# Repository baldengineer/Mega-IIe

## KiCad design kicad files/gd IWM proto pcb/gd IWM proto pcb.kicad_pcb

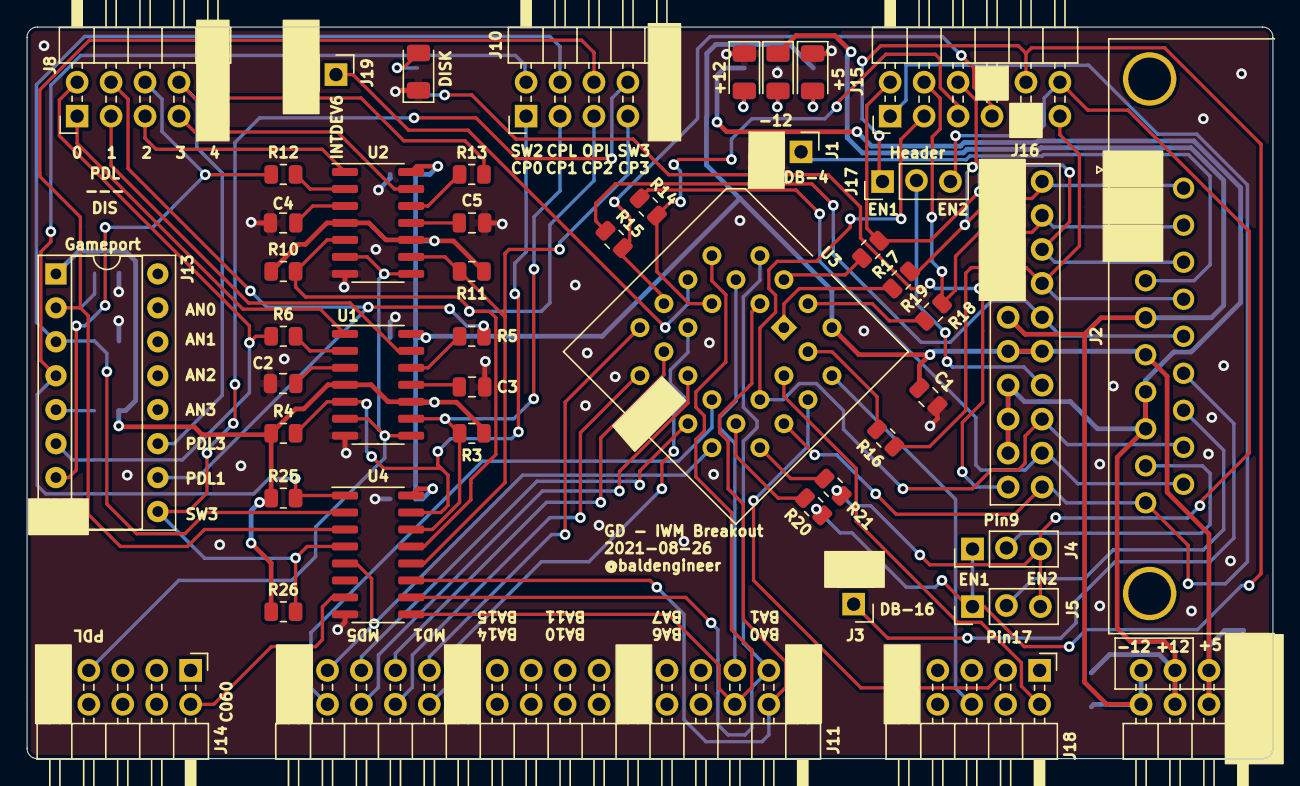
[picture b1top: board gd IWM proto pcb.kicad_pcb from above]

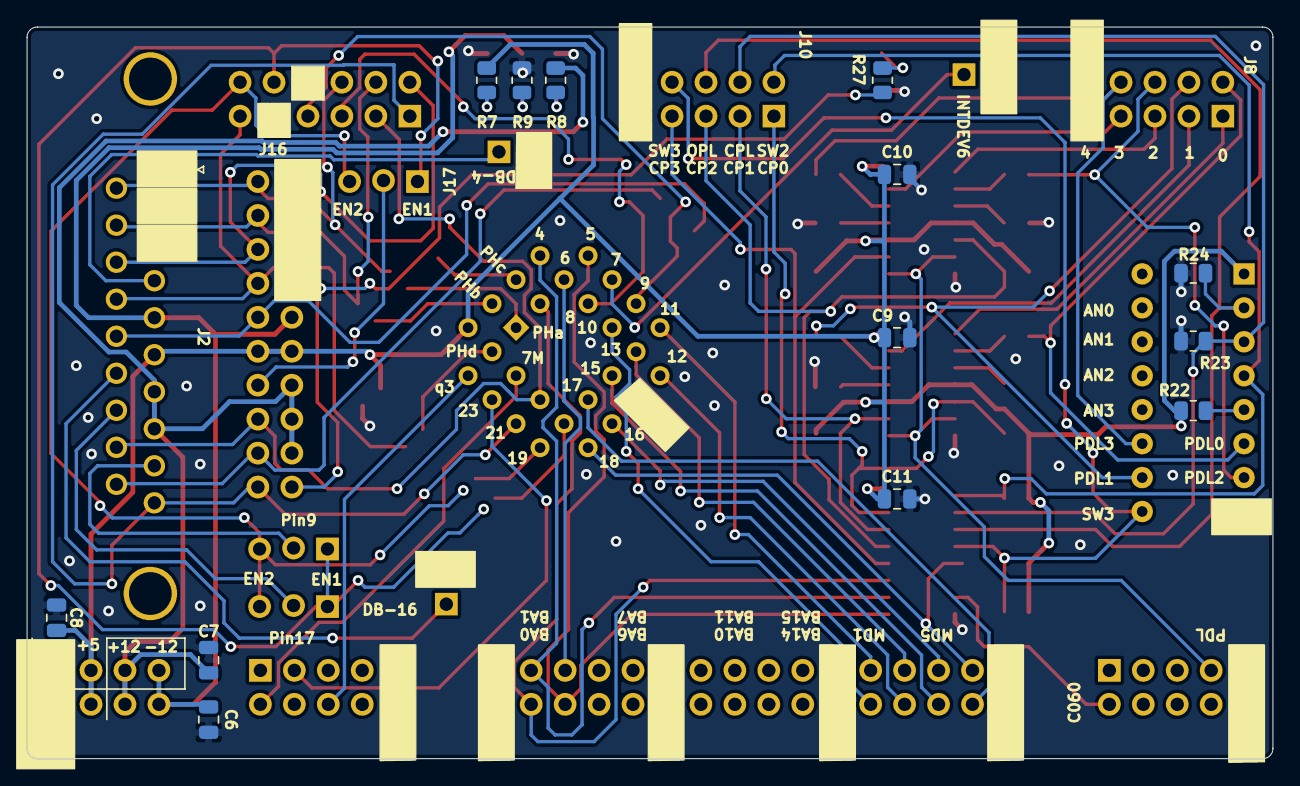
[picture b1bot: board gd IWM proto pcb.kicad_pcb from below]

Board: 2 copper layers, 93.2 x 54.7 mm, 60 parts (13 on the bottom side), 75 nets.

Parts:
C1, C6, C7, C8: 10u; C_0805_2012Metric
C2, C3, C4, C5: .1u; C_0805_2012Metric
C9, C10, C11: 1u; C_0805_2012Metric
D2: -5v; LED_1206_3216Metric
D3: +5v; LED_1206_3216Metric
D4: +12v; LED_1206_3216Metric
D5: DSK; LED_1206_3216Metric
J1: DB19_4; PinHeader_1x02_P2.54mm_Vertical-LOCK
J2: DSUB19; DSUB-19_Apple_II_Floppy
J3: DB19_16; PinHeader_1x02_P2.54mm_Vertical-LOCK
J4, J5, J17: EN; PinHeader_1x03_P2.54mm_Vertical-LOCK
J6: PWR; PinHeader_2x04_P2.54mm_Horizontal
J8: 555_LA; PinHeader_2x05_P2.54mm_Horizontal
J10: CPx_LA; PinHeader_2x05_P2.54mm_Horizontal
J11: Addr_Main_Data; PinHeader_2x16_P2.54mm_Horizontal
J13: Game Port; DIP-16_W7.62mm_Socket
J14: CTRL2; PinHeader_2x05_P2.54mm_Horizontal
J15: IWM-LA; PinHeader_2x06_P2.54mm_Horizontal
J16: FDC Hdr; PinHeader_2x10_P2.54mm_Vertical
J18: CTRL1; PinHeader_2x05_P2.54mm_Horizontal
J19: Slot_Maker; PinHeader_1x02_P2.54mm_Vertical-LOCK
R3, R4, R10, R11: 1K; R_0805_2012Metric
R5, R6, R12, R13: 100; R_0805_2012Metric
R7, R8, R9: 1k; R_0805_2012Metric
R14, R15, R16, R17, R18, R19, R20, R21: 22; R_0805_2012Metric
R22, R23, R24, R27: 4k7; R_0805_2012Metric
R25, R26: 200k; R_0805_2012Metric
U1, U2: NE556; SO-14_3.9x8.65mm_P1.27mm
U3: IWM; PLCC-28_THT-Socket
U4: HCT251; SOIC-16_3.9x9.9mm_P1.27mm

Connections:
+5V: C1.1, C8.1, C9.1, C10.1, C11.1, J2.6, J6.3, J6.4, J13.1, J16.11, J16.12, R3.1, R4.1, R7.1, R10.1, R11.1, R22.1, R25.1, R26.1, U1.4, U1.10, U1.14, U2.4, U2.10, U2.14, U3.26, U4.16
+12V: C7.1, J2.7, J2.8, J6.5, J6.6, J16.13, J16.15, J16.17, R8.1
-12V: C6.1, D2.1, J2.5, J6.7, J6.8, J16.9
/7M: J18.2, U3.24
/BA0: J11.4, U3.3, U4.11
/BA1: J11.3, U3.4, U4.10
/BA2: J11.6, U3.5, U4.9
/BA3: J11.5, U3.6
/C060-67: J14.2, U4.7
/CP0: J10.1, R4.2, U1.5, U4.15
/CP1: J10.3, R3.2, U1.9, U4.14
/CP2: J10.5, R10.2, U2.5, U4.13
/CP3: J10.7, R11.2, U2.9, U4.12
/DB19-4: J1.1, J2.4
/DB19-16: J2.16, J3.1
/DIS0: J8.1, U1.1
/DIS1: J8.3, U1.13
/DIS2: J8.5, U2.1
/DIS3: J8.7, U2.13
/DiskAct: J16.19, R27.1
/EN1: R20.2, U3.20
/EN2: R21.2, U3.19
/INTDEV6: J19.1, U3.7
/MD0: J11.24, U3.10
/MD1: J11.23, U3.11
/MD2: J11.26, U3.12
/MD3: J11.25, U3.13
/MD4: J11.28, U3.15
/MD5: J11.27, U3.16
/MD6: J11.30, U3.17
/MD7: J11.29, U3.18, U4.5
/PDL0: J8.2, J13.6, R6.1
/PDL1: J8.4, J13.10, R5.1
/PDL2: J8.6, J13.7, R12.1
/PDL3: J8.8, J13.11, R13.1
/PDLTRIG: J14.7, U1.6, U1.8, U2.6, U2.8
/PHa: R19.2, U3.1
/PHb: R18.2, U3.28
/PHc: R17.2, U3.2
/PHd: R16.2, U3.27
/Q3: J18.6, U3.25
/RDATA: J2.18, J15.3, J16.16, U3.22
/RESET: J18.3, U3.23
/SENSE: J2.10, J15.1, J16.20, U3.21
/STB: J13.5, R22.2
/SW0_OAPL: J10.6, J13.2, R24.1, U4.3
/SW1_CAPL: J10.4, J13.3, R23.1, U4.2
/SW2: J10.2, J13.4, R25.2, U4.1
/SW3: J10.8, J13.9, R26.2, U4.4
/WDATA: J15.5, R14.2, U3.8
/WREQ: J15.7, R15.2, U3.9
/bEN1: J4.1, J5.1, J15.10, J17.1, R20.1
/bEN2: J4.3, J5.3, J15.12, J17.3, R21.1
/bWDATA: J2.19, J16.18, R14.1
/bWREQ: J2.15, J16.10, R15.1
/seek0: J2.11, J15.6, J16.2, R19.1
/seek1: J2.12, J15.4, J16.4, R18.1
/seek2: J2.13, J15.2, J16.6, R17.1
/seek3: J2.14, J15.11, J16.8, R16.1
GND: C1.2, C2.2, C3.2, C4.2, C5.2, C6.2, C7.2, C8.2, C9.2, C10.2, C11.2, D3.1, D4.1, D5.1, J1.2, J2.1, J2.2, J2.3, J3.2, J6.1, J6.2, J8.9, J8.10, J10.9, J10.10, J11.1, J11.2, J11.11, J11.12, J11.21, J11.22, J11.31, J11.32, J13.8, J14.9, J14.10, J15.8, J15.9, J16.1, J16.3, J16.5, J16.7, J18.9, J18.10, J19.2, R9.1, R23.2, R24.2, U1.7, U2.7, U3.14, U4.8
unnamed: C2.1, U1.3
unnamed: C3.1, U1.11
unnamed: C4.1, U2.3
unnamed: C5.1, U2.11
unnamed: D2.2, R9.2
unnamed: D3.2, R7.2
unnamed: D4.2, R8.2
unnamed: D5.2, R27.2
unnamed: J2.9, J4.2
unnamed: J2.17, J5.2
unnamed: J16.14, J17.2
unnamed: R5.2, U1.12
unnamed: R6.2, U1.2
unnamed: R12.2, U2.2
unnamed: R13.2, U2.12

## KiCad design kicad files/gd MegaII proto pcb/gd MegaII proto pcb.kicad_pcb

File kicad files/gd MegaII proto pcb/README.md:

## gd MegaII proto pcb
This board is the center piece. It contains the MEGA-II and has all of its signals broken out to multiple headers. 

It connects to both the VGC and 6502 boards. The VGC connects with a 40-pin cable, like an IDE cable. The 6502 connects with a couple of ribbon cables.

Runs off of 5V.

## Rev1 Notes:
* Nothing... yet :)

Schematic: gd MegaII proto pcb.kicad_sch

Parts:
C1: 100nF; C_0805_2012Metric
C2: 100uF; CP_Radial_D8.0mm_P5.00mm
C3, C4, C5, C6, C7, C8, C9, C11: 1uF; C_0805_2012Metric
C10: 10uF; C_0805_2012Metric
D1: PWR; LED_1206_3216Metric
H1, H2, H3, H4: MountingHole; MountingHole_2.5mm
J1: ABDIR; PinHeader_1x03_P2.54mm_Vertical
J2: ABEN; PinHeader_1x03_P2.54mm_Vertical
J3: FLIP; PinHeader_1x03_P2.54mm_Vertical
J4: DBDIR; PinHeader_1x03_P2.54mm_Vertical
J5: DBEN; PinHeader_1x03_P2.54mm_Vertical
J6: VGC Extra 1; PinHeader_1x03_P2.54mm_Vertical
J7: Bald-Ext-1; PinHeader_2x20_P2.54mm_Vertical
J8: VGC Extra 2; PinHeader_1x03_P2.54mm_Vertical
J9: Address; PinHeader_2x10_P2.54mm_Vertical
J10: Data; PinHeader_2x05_P2.54mm_Vertical
J11: PWR; PinHeader_1x04_P2.54mm_Vertical
J12: CLKS; PinHeader_1x04_P2.54mm_Vertical
JP1: RGB Binary; PinHeader_1x04_P2.54mm_Vertical
JP3, JP7, JP12, JP16: P54-63; PinHeader_1x10_P2.54mm_Vertical
JP4, JP8, JP11, JP15: P64-74; PinHeader_1x11_P2.54mm_Vertical
R1: 1k; R_0805_2012Metric
R14, R15: 100; R_0805_2012Metric
RN1, RN2, RN3, RN4, RN5, RN6: R_Pack04; R_Array_Convex_4x0612
RN7, RN8, RN9: 100; R_Array_Convex_4x0612
TP97, TP98: TestPoint; Harwin-S1751-46-Test-Point
U1: Apple_MEGA_II; PLCC-84_THT-Socket
U2, U4, U7, U9: DRAM64KX4; DIP-18_W7.62mm_Socket_LongPads
U3, U5, U8: 74HCT245; SOIC-20W_7.5x12.8mm_P1.27mm
U6: 74HCT86; SOIC-14_3.9x8.7mm_P1.27mm

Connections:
+5V: C1.1, C2.1, C3.1, C4.1, C5.1, C6.1, C7.1, C8.1, C9.1, C10.1, C11.1, J1.1, J2.1, J4.1, J5.1, J11.1, J11.2, JP12.3, R1.1, U1.77 (VDD), U2.9 (VCC), U3.20 (+V), U4.9 (VCC), U5.20 (+V), U6.14 (VCC), U7.9 (VCC), U8.20 (+V), U9.9 (VCC)
/7M: J12.4, JP12.4, U1.78 (7M)
/14M: J7.2, JP12.2, U1.76 (14M)
/A0: J9.1, RN1.1 (R1.1), U5.9 (A8)
/A1: J9.2, RN1.2 (R2.1), U5.8 (A7)
/A2: J9.3, RN1.3 (R3.1), U5.7 (A6)
/A3: J9.6, RN1.4 (R4.1), U5.6 (A5)
/A4: J9.5, RN4.1 (R1.1), U5.5 (A4)
/A5: J9.8, RN4.2 (R2.1), U5.4 (A3)
/A6: J9.9, RN4.3 (R3.1), U5.3 (A2)
/A7: J9.10, RN4.4 (R4.1), U5.2 (A1)
/A8: J9.11, RN2.1 (R1.1), U3.9 (A8)
/A9: J9.14, RN2.2 (R2.1), U3.8 (A7)
/A10: J9.13, RN2.3 (R3.1), U3.7 (A6)
/A11: J9.16, RN2.4 (R4.1), U3.6 (A5)
/A12: J9.17, RN5.1 (R1.1), U3.5 (A4)
/A13: J9.18, RN5.2 (R2.1), U3.4 (A3)
/A14: J9.19, RN5.3 (R3.1), U3.3 (A2)
/A15: J9.20, RN5.4 (R4.1), U3.2 (A1)
/ABDIR: J1.2, U3.1 (DIR), U5.1 (DIR)
/ABEN: J2.2, U3.19 (G), U5.19 (G)
/AD0: J7.15, JP4.1, U1.22 (AD0), U2.2 (IQ0)
/AD1: J7.13, JP4.2, U1.23 (AD1), U2.3 (IQ1)
/AD2: J7.12, JP4.3, U1.24 (AD2), U2.15 (IQ2)
/AD3: J7.9, JP4.4, U1.25 (AD3), U2.17 (IQ3)
/AD4: J7.10, JP4.5, U1.26 (AD4), U4.2 (IQ0)
/AD5: J7.7, JP4.6, U1.27 (AD5), U4.3 (IQ1)
/AD6: J7.8, JP4.7, U1.28 (AD6), U4.15 (IQ2)
/AD7: J7.5, JP4.8, U1.29 (AD7), U4.17 (IQ3)
/BA0: JP15.3, RN1.8 (R1.2), U1.66 (A0), U5.11 (B8)
/BA1: JP15.2, RN1.7 (R2.2), U1.65 (A1), U5.12 (B7)
/BA2: JP15.1, RN1.6 (R3.2), U1.64 (A2), U5.13 (B6)
/BA3: JP16.10, RN1.5 (R4.2), U1.63 (A3), U5.14 (B5)
/BA4: JP16.9, RN4.8 (R1.2), U1.62 (A4), U5.15 (B4)
/BA5: JP16.8, RN4.7 (R2.2), U1.61 (A5), U5.16 (B3)
/BA6: JP16.7, RN4.6 (R3.2), U1.60 (A6), U5.17 (B2)
/BA7: JP16.6, RN4.5 (R4.2), U1.59 (A7), U5.18 (B1)
/BA8: JP16.5, RN2.8 (R1.2), U1.58 (A8), U3.11 (B8)
/BA9: JP16.4, RN2.7 (R2.2), U1.57 (A9), U3.12 (B7)
/BA10: JP16.3, RN2.6 (R3.2), U1.56 (A10), U3.13 (B6)
/BA11: JP16.2, RN2.5 (R4.2), U1.55 (A11), U3.14 (B5)
/BA12: J8.2, JP16.1, RN5.8 (R1.2), U1.54 (A12), U3.15 (B4)
/BA13: JP11.11, RN5.7 (R2.2), U1.53 (A13), U3.16 (B3)
/BA14: JP11.10, RN5.6 (R3.2), U1.52 (A14), U3.17 (B2)
/BA15: JP11.9, RN5.5 (R4.2), U1.51 (A15), U3.18 (B1)
/C060-67: JP8.11, U1.11 (~C060-67)
/CASA: JP12.8, RN9.2 (R2.1), U1.82 (~CASA)
/CASA.B: RN9.7 (R2.2), U2.16 (~CAS), U4.16 (~CAS)
/CASM: JP12.9, RN9.1 (R1.1), U1.83 (~CASM)
/CASM.B: RN9.8 (R1.2), U7.16 (~CAS), U9.16 (~CAS)
/CREF: J12.3, JP12.5, U1.79 (CREF)
/D0: J10.1, RN3.4 (R4.1), U8.2 (A1)
/D1: J10.2, RN3.3 (R3.1), U8.3 (A2)
/D2: J10.3, RN3.2 (R2.1), U8.4 (A3)
/D3: J10.4, RN3.1 (R1.1), U8.5 (A4)
/D4: J10.7, RN6.4 (R4.1), U8.6 (A5)
/D5: J10.6, RN6.3 (R3.1), U8.7 (A6)
/D6: J10.9, RN6.2 (R2.1), U8.8 (A7)
/D7: J10.10, RN6.1 (R1.1), U8.9 (A8)
/DBDIR: J4.2, U8.1 (DIR)
/DBEN: J5.2, U8.19 (G)
/DMA: JP7.6, U1.38 (~DMA)
/FLIP6: J3.3, U6.2
/FLIP7: J3.1, U6.5
/INH: JP7.8, U1.40 (~INH)
/IRQ: J6.1, JP3.4, U1.15 (~IRQ)
/KSEL1: JP3.2, U1.13 (~KSEL1)
/KSEL2: JP3.3, U1.14 (~KSEL2)
/M2SEL: J8.3, JP7.7, U1.39 (~M2SEL)
/MD0: J7.16, JP8.9, RN3.5 (R4.2), U1.9 (MD0), U7.2 (IQ0), U8.18 (B1)
/MD1: J7.18, JP8.8, RN3.6 (R3.2), U1.8 (MD1), U7.3 (IQ1), U8.17 (B2)
/MD2: J7.24, JP8.7, RN3.7 (R2.2), U1.7 (MD2), U7.15 (IQ2), U8.16 (B3)
/MD3: J7.26, JP8.6, RN3.8 (R1.2), U1.6 (MD3), U7.17 (IQ3), U8.15 (B4)
/MD4: J7.28, JP8.5, RN6.5 (R4.2), U1.5 (MD4), U8.14 (B5), U9.2 (IQ0)
/MD5: J7.32, JP8.4, RN6.6 (R3.2), U1.4 (MD5), U8.13 (B6), U9.3 (IQ1)
/MD6: J7.34, JP8.3, RN6.7 (R2.2), U1.3 (MD6), U8.12 (B7), U9.15 (IQ2)
/MD7: J7.36, JP8.2, RN6.8 (R1.2), U1.2 (MD7), U8.11 (B8), U9.17 (IQ3)
/MDI-MDO: JP7.4, U1.36 (MDIN/OUT)
/MSW: JP3.9, U1.20 (~MSW)
/PDLTRIG: JP8.10, U1.10 (~PDLTRIG)
/PH#: J7.39, J12.1, JP12.7, U1.81 (PH#)
/Q3: J12.2, JP12.6, U1.80 (Q3)
/R-W: J6.3, JP7.9, U1.41 (R/W)
/RA0: J7.17, JP15.11, RN7.1 (R1.1), U1.74 (RA0)
/RA1: J7.21, JP15.10, RN8.1 (R1.1), U1.73 (RA1)
/RA2: J7.23, JP15.9, RN8.3 (R3.1), U1.72 (RA2)
/RA3: J7.25, JP15.8, RN7.2 (R2.1), U1.71 (RA3)
/RA4: J7.29, JP15.7, RN8.4 (R4.1), U1.70 (RA4)
/RA5: J7.31, JP15.6, RN8.2 (R2.1), U1.69 (RA5)
/RA6: J7.33, JP15.5, RN7.3 (R3.1), U1.68 (RA6), U6.1
/RA7: J7.35, JP15.4, RN7.4 (R4.1), U1.67 (RA7), U6.4
/RAF0: RN7.8 (R1.2), U2.6 (A0), U4.6 (A0), U7.6 (A0), U9.6 (A0)
/RAF1: RN8.8 (R1.2), U2.8 (A1), U4.8 (A1), U7.8 (A1), U9.8 (A1)
/RAF2: RN8.6 (R3.2), U2.7 (A2), U4.7 (A2), U7.7 (A2), U9.7 (A2)
/RAF3: RN7.7 (R2.2), U2.13 (A3), U4.13 (A3), U7.13 (A3), U9.13 (A3)
/RAF4: RN8.5 (R4.2), U2.12 (A4), U4.12 (A4), U7.12 (A4), U9.12 (A4)
/RAF5: RN8.7 (R2.2), U2.11 (A5), U4.11 (A5), U7.11 (A5), U9.11 (A5)
/RAF6: RN7.6 (R3.2), U2.14 (A6), U4.14 (A6)
/RAF7: RN7.5 (R4.2), U2.10 (A7), U4.10 (A7)
/RAMWE: JP8.1, RN9.4 (R4.1), U1.1 (~RAMWE)
/RAS: JP12.10, RN9.3 (R3.1), U1.84 (~RAS)
/RAS.B: RN9.6 (R3.2), U2.5 (~RAS), U4.5 (~RAS), U7.5 (~RAS), U9.5 (~RAS)
/RESET: J6.2, JP7.3, U1.35 (~RESET)
/RGB1: JP1.3, JP7.2, U1.34 (RGB1)
/RGB2: JP1.4, JP4.11, U1.32 (RGB2)
/RGB4: JP1.1, JP4.10, U1.31 (RGB4)
/RGB8: JP1.2, JP4.9, U1.30 (RGB8)
/RMBK: JP11.6, U1.48 (RMBK/BA0)
/ROMEN: JP7.5, U1.37 (~ROMEN)
/RWE.B: RN9.5 (R4.2), U2.4 (R/~W), U4.4 (R/~W), U7.4 (R/~W), U9.4 (R/~W)
/S0: JP7.10, U1.42 (S0)
/S1: JP11.1, U1.43 (S1)
/S2: JP11.2, U1.44 (S2)
/S3: JP11.3, U1.45 (S3)
/S4: JP11.4, U1.46 (S4)
/S5: JP11.5, U1.47 (S5)
/SERVIDEO: JP3.10, U1.21 (SERVIDEO)
/SPKR: JP3.1, U1.12 (SPKR)
/SYNC: JP11.8, U1.50 (~SYNC)
/UM4-10: R15.1, U7.10 (A7), U9.10 (A7)
/UM4-14: R14.1, U7.14 (A6), U9.14 (A6)
/WINDOW: JP11.7, U1.49 (~WINDOW)
/X0: JP3.5, U1.16 (X0)
/X1: JP3.6, U1.17 (X1)
/Y0: JP3.7, U1.18 (Y0)
/Y1: JP3.8, U1.19 (Y1)
GND: C1.2, C2.2, C3.2, C4.2, C5.2, C6.2, C7.2, C8.2, C9.2, C10.2, C11.2, D1.1 (K), J1.3, J2.3, J3.2, J4.3, J5.3, J7.1, J7.3, J7.4, J7.6, J7.11, J7.14, J7.19, J7.22, J7.27, J7.30, J7.37, J7.38, J7.40, J8.1, J9.4, J9.7, J9.12, J9.15, J10.5, J10.8, J11.3, J11.4, JP7.1, JP12.1, U1.33 (GND), U1.75 (GND), U2.1 (~OE), U2.18 (VSS), U3.10 (GND), U4.1 (~OE), U4.18 (VSS), U5.10 (GND), U6.7 (GND), U7.1 (~OE), U7.18 (VSS), U8.10 (GND), U9.1 (~OE), U9.18 (VSS)
unnamed: D1.2 (A), R1.2
unnamed: R14.2, TP97.1, U6.3
unnamed: R15.2, TP98.1, U6.6

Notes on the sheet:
FLIP6 and FLIP7 come from VGC board

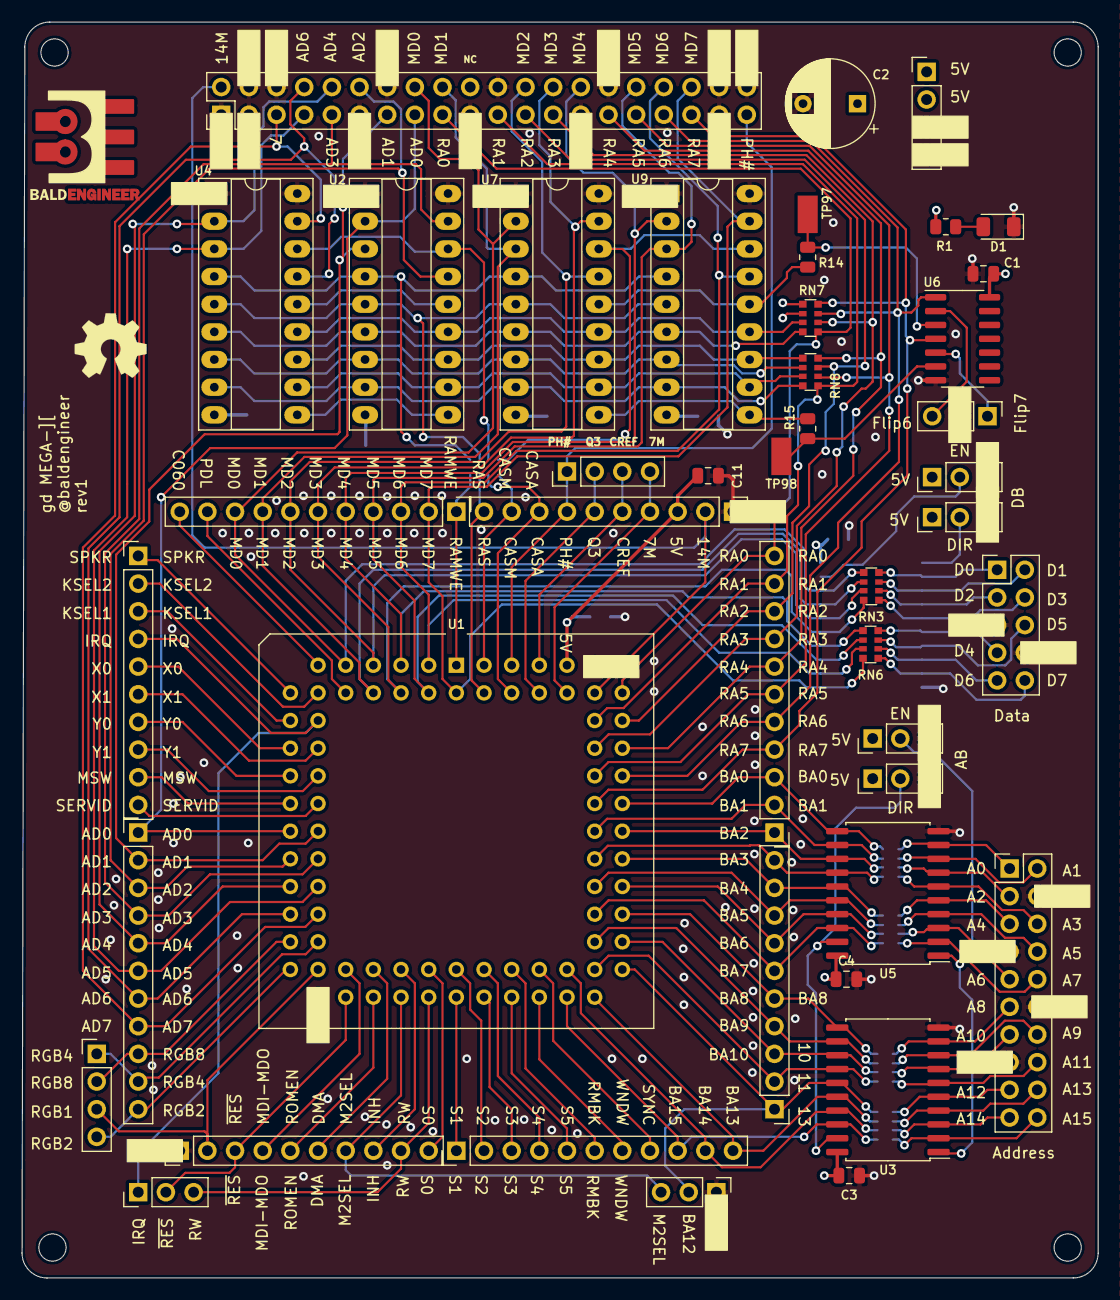
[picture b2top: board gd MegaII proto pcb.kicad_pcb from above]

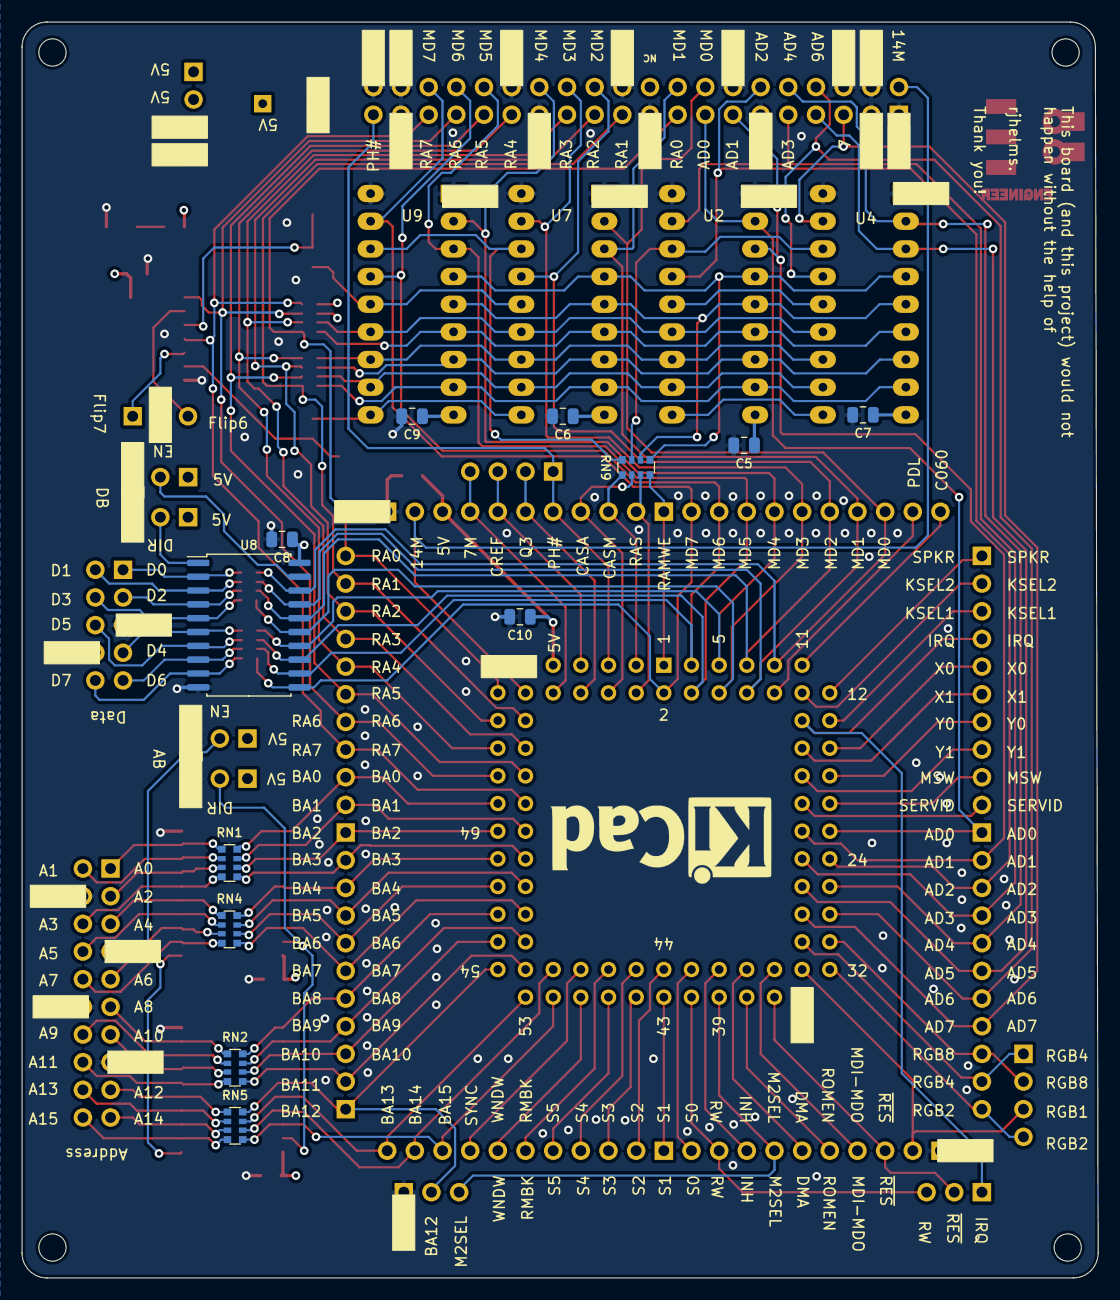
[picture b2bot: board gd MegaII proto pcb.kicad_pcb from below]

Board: 4 copper layers, 98.8 x 115.3 mm, 61 parts (12 on the bottom side), 130 nets.

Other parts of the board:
svg2mod: G***; BE10v2

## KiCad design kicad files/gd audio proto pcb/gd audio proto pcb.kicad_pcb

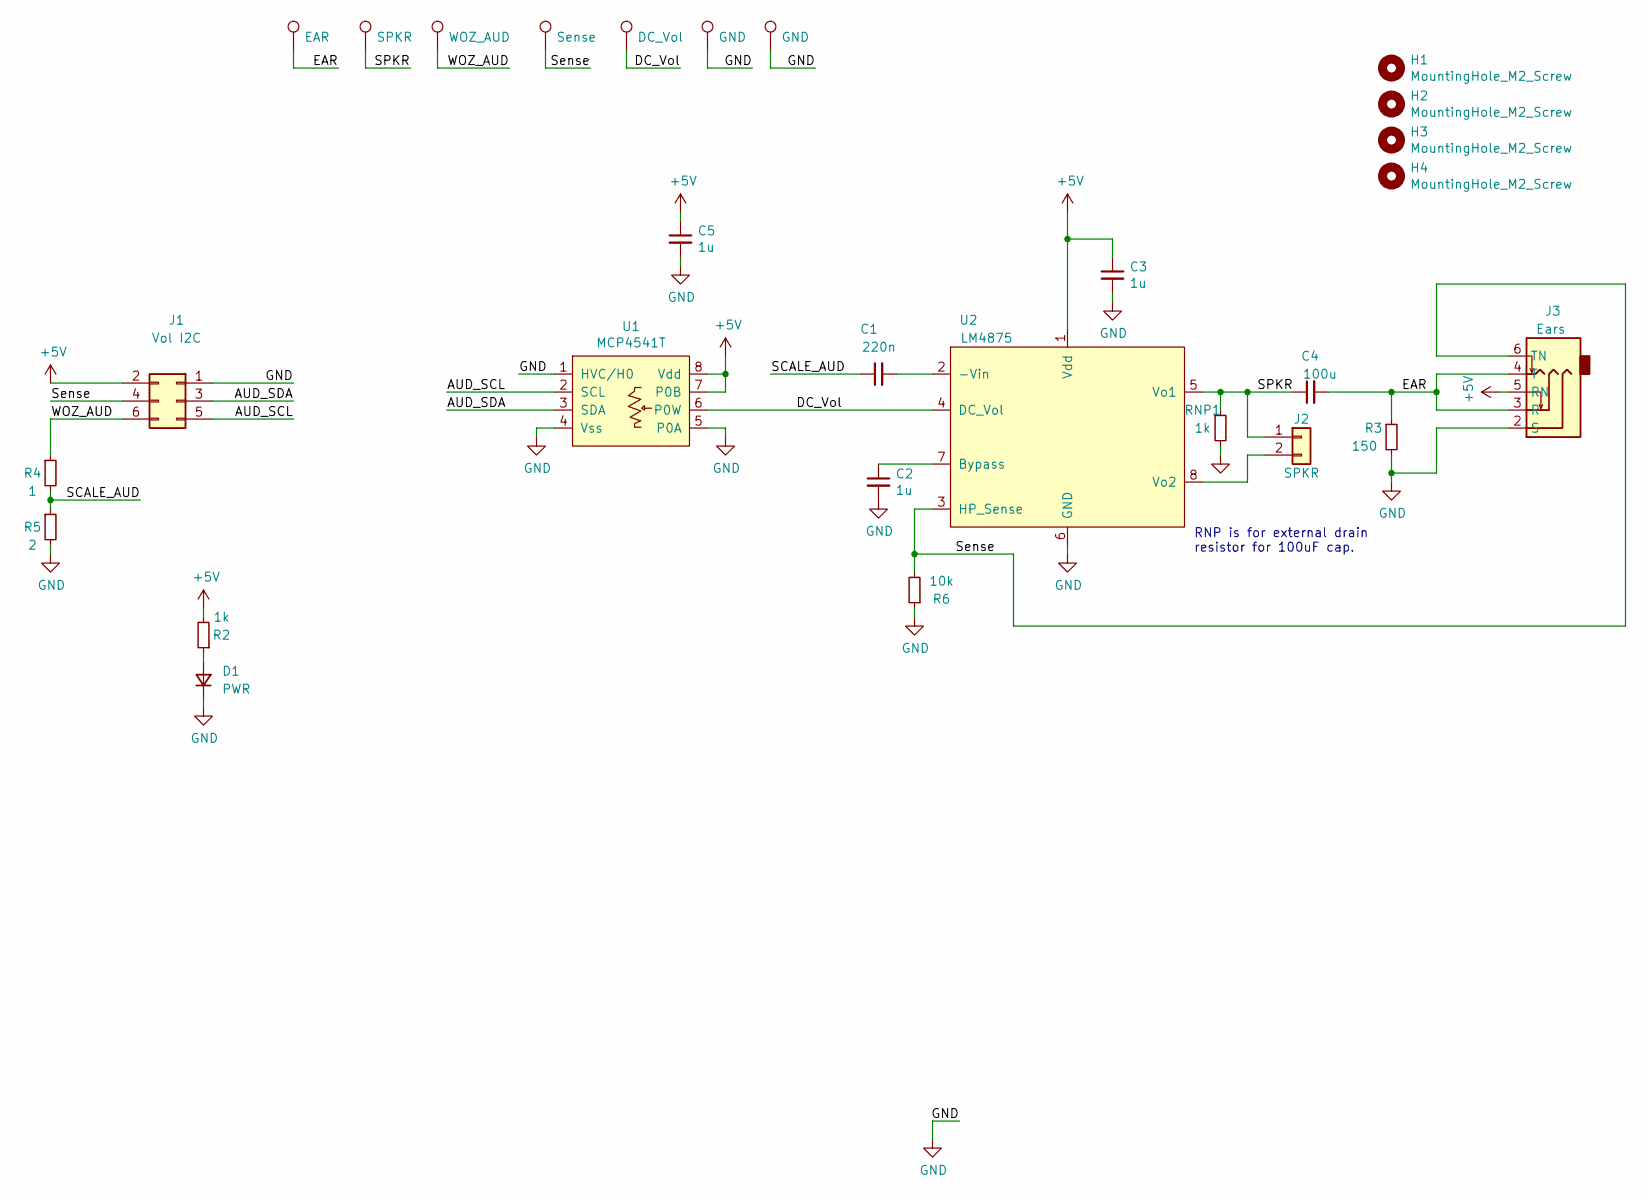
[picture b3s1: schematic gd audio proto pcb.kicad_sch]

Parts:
C1: 220n; R_1206_3216Metric
C2, C3, C5: 1u; R_0805_2012Metric
C4: 100u; CP_EIA-3216-18_Kemet-A; MPN T520A107M006ATE035
D1: PWR; LED_1206_3216Metric
H1, H2, H3, H4: MountingHole_M2_Screw; MountingHole_2.2mm_M2
J1: Vol I2C; PinHeader_2x03_P2.54mm_Vertical
J2: SPKR; PinHeader_1x02_P2.54mm_Vertical
J3: Ears; Jack_3.5mm_PJ311_Horizontal; MPN 54-00178
R2: 1k; R_0805_2012Metric
R3: 150; R_0805_2012Metric
R4: 1; R_0805_2012Metric
R5: 2; R_0805_2012Metric
R6: 10k; R_0805_2012Metric
RNP1: 1k; R_0805_2012Metric
TP1: EAR; Harwin-S1751-46-Test-Point
TP2: SPKR; Harwin-S1751-46-Test-Point
TP3: WOZ_AUD; Harwin-S1751-46-Test-Point
TP4: Sense; Harwin-S1751-46-Test-Point
TP5: DC_Vol; Harwin-S1751-46-Test-Point
TP6, TP7: GND; Harwin-S1751-46-Test-Point
U1: MCP4541T; MSOP-8_3x3mm_P0.65mm
U2: LM4875; SOIC-8_3.9x4.9mm_P1.27mm

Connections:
+5V: C3.1, C5.1, J1.2, J3.5 (RN), R2.2, U1.7 (P0B), U1.8 (Vdd), U2.1 (Vdd)
/AUD_SCL: J1.5, U1.2 (SCL)
/AUD_SDA: J1.3, U1.3 (SDA)
/DC_Vol: TP5.1, U1.6 (P0W), U2.4 (DC_Vol)
/EAR: C4.2, J3.3 (R), J3.4 (T), R3.1, TP1.1
/SCALE_AUD: C1.1, R4.2, R5.1
/SPKR: C4.1, J2.1, RNP1.1, TP2.1, U2.5 (Vo1)
/Sense: J1.4, J3.6 (TN), R6.2, TP4.1, U2.3 (HP_Sense)
/WOZ_AUD: J1.6, R4.1, TP3.1
GND: C2.2, C3.2, C5.2, D1.1 (K), J1.1, J3.2 (S), R3.2, R5.2, R6.1, RNP1.2, TP6.1, TP7.1, U1.1 (HVC/H0), U1.4 (Vss), U1.5 (P0A), U2.6 (GND)
unnamed: C1.2, U2.2 (-Vin)
unnamed: C2.1, U2.7 (Bypass)
unnamed: D1.2 (A), R2.1
unnamed: J2.2, U2.8 (Vo2)

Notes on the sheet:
RNP is for external drain resistor for 100uF cap.

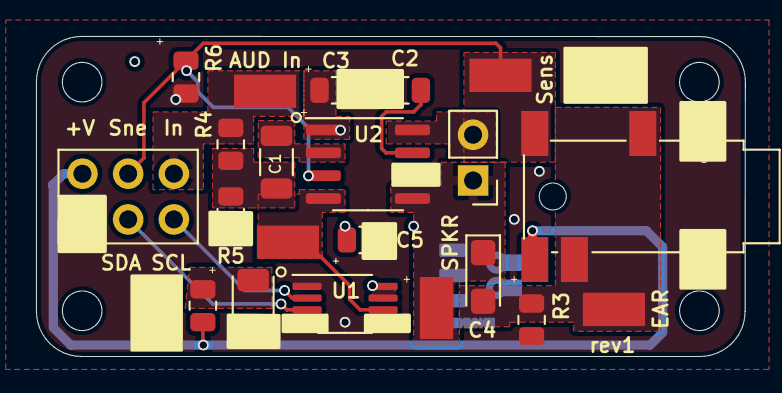
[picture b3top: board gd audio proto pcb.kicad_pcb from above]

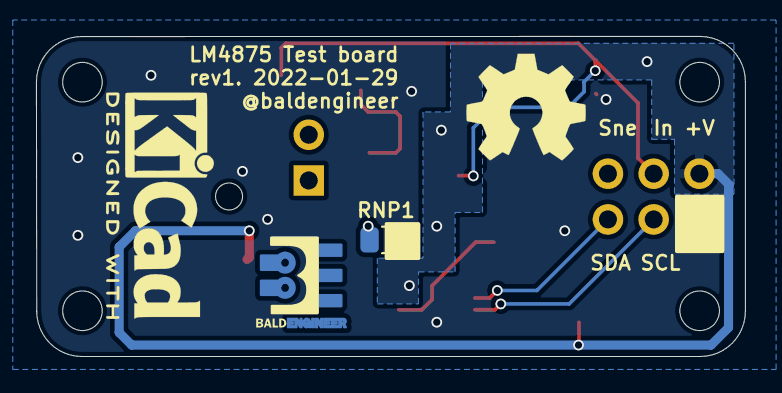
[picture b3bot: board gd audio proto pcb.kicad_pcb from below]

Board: 2 copper layers, 39.4 x 17.8 mm, 29 parts (2 on the bottom side), 14 nets.

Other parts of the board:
svg2mod: G***; BE5v2

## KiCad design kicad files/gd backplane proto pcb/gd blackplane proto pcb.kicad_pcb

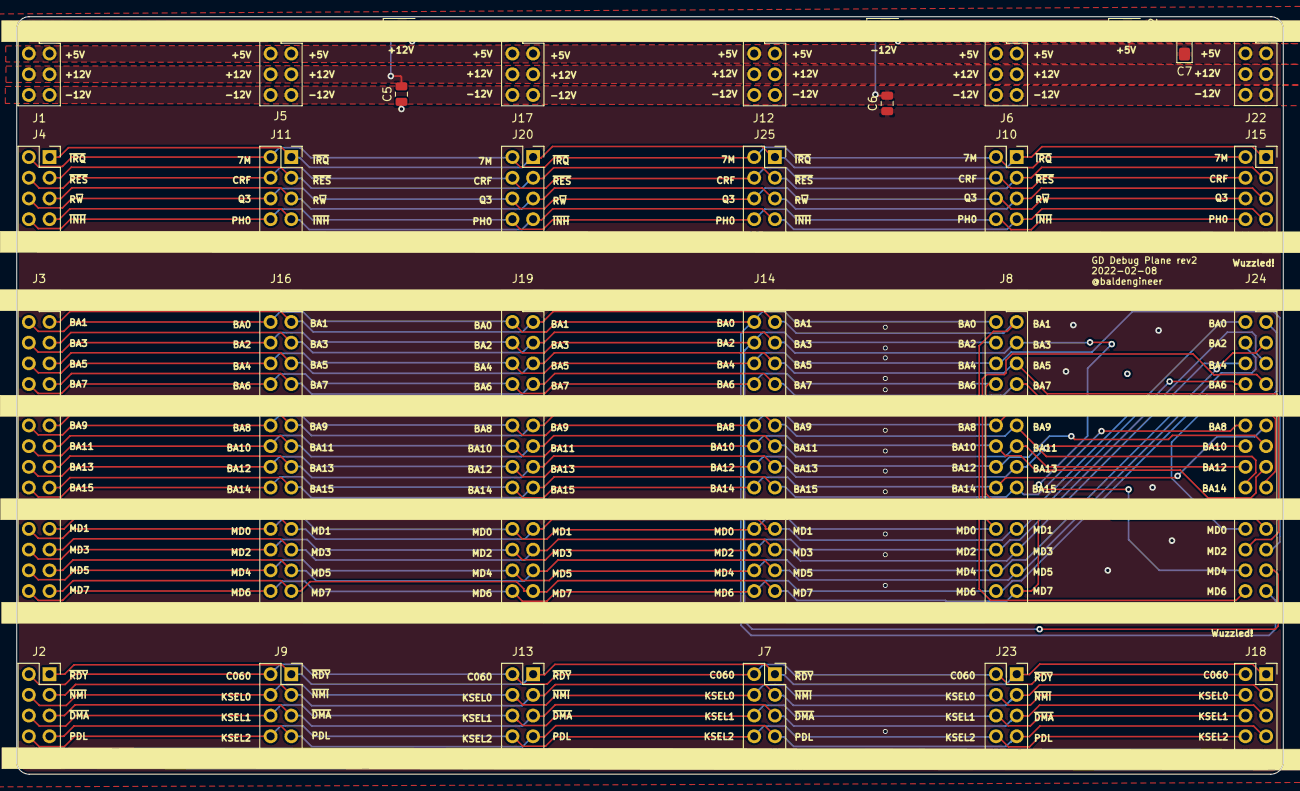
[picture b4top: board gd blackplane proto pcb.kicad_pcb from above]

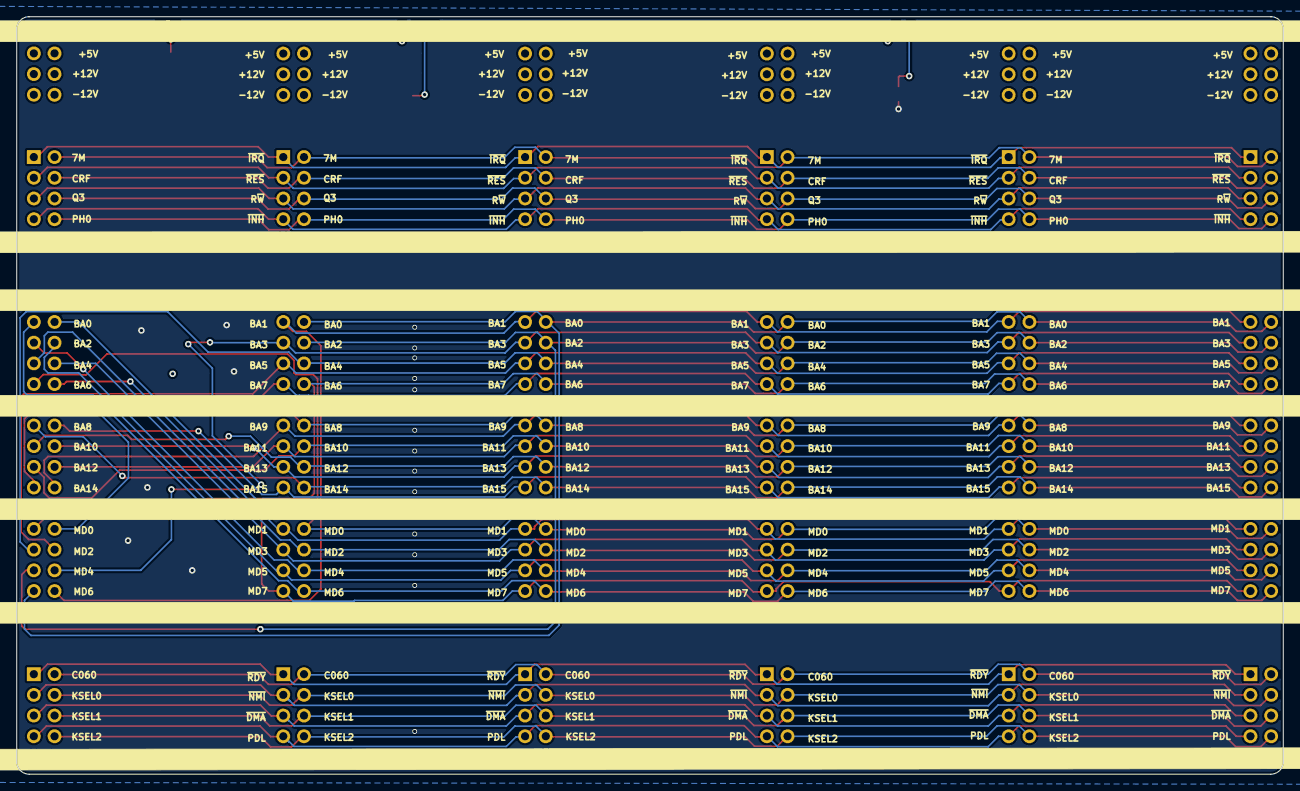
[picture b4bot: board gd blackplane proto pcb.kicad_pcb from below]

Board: 2 copper layers, 155.4 x 93.0 mm, 33 parts (3 on the bottom side), 47 nets.

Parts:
C5: 10uF; C_0805_2012Metric
C6: 100nF; C_0805_2012Metric
C7: 100uF; CP_EIA-3216-18_Kemet-A_Pad1.58x1.35mm_HandSolder
D1: +12; LED_1206_3216Metric
D2: +5; LED_1206_3216Metric
D3: -12; LED_1206_3216Metric
J1, J5, J6, J12, J17, J22: Pwr; PinSocket_2x04_P2.54mm_Vertical
J2, J7, J9, J13, J18, J23: CTRL2; PinSocket_2x05_P2.54mm_Vertical
J3, J8, J14, J16, J19, J24: Addr_Main_Data; PinSocket_2x16_P2.54mm_Vertical
J4, J10, J11, J15, J20, J25: CTRL1; PinSocket_2x05_P2.54mm_Vertical
R1, R2, R3: 1k; R_0805_2012Metric

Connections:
+5V: C7.1, J1.3, J1.4, J5.3, J5.4, J6.3, J6.4, J12.3, J12.4, J17.3, J17.4, J22.3, J22.4, R2.1
+12V: C5.1, J1.5, J1.6, J5.5, J5.6, J6.5, J6.6, J12.5, J12.6, J17.5, J17.6, J22.5, J22.6, R1.1
-12V: C6.1, D3.1, J1.7, J1.8, J5.7, J5.8, J6.7, J6.8, J12.7, J12.8, J17.7, J17.8, J22.7, J22.8
/7M: J4.2, J10.2, J11.2, J15.2, J20.2, J25.2
/BA0: J3.4, J8.4, J14.4, J16.4, J19.4, J24.29
/BA1: J3.3, J8.3, J14.3, J16.3, J19.3, J24.30
/BA2: J3.6, J8.6, J14.6, J16.6, J19.6, J24.27
/BA3: J3.5, J8.5, J14.5, J16.5, J19.5, J24.28
/BA4: J3.8, J8.8, J14.8, J16.8, J19.8, J24.25
/BA5: J3.7, J8.7, J14.7, J16.7, J19.7, J24.26
/BA6: J3.10, J8.10, J14.10, J16.10, J19.10, J24.23
/BA7: J3.9, J8.9, J14.9, J16.9, J19.9, J24.24
/BA8: J3.14, J8.14, J14.14, J16.14, J19.14, J24.19
/BA9: J3.13, J8.13, J14.13, J16.13, J19.13, J24.20
/BA10: J3.16, J8.16, J14.16, J16.16, J19.16, J24.17
/BA11: J3.15, J8.15, J14.15, J16.15, J19.15, J24.18
/BA12: J3.18, J8.18, J14.18, J16.18, J19.18, J24.15
/BA13: J3.17, J8.17, J14.17, J16.17, J19.17, J24.16
/BA14: J3.20, J8.20, J14.20, J16.20, J19.20, J24.13
/BA15: J3.19, J8.19, J14.19, J16.19, J19.19, J24.14
/C060-67: J2.2, J7.2, J9.2, J13.2, J18.2, J23.2
/CREF: J4.4, J10.4, J11.4, J15.4, J20.4, J25.4
/KSEL0: J2.4, J7.4, J9.4, J13.4, J18.4, J23.4
/KSEL1: J2.6, J7.6, J9.6, J13.6, J18.6, J23.6
/KSEL2: J2.8, J7.8, J9.8, J13.8, J18.8, J23.8
/MD0: J3.24, J8.24, J14.24, J16.24, J19.24, J24.9
/MD1: J3.23, J8.23, J14.23, J16.23, J19.23, J24.10
/MD2: J3.26, J8.26, J14.26, J16.26, J19.26, J24.7
/MD3: J3.25, J8.25, J14.25, J16.25, J19.25, J24.8
/MD4: J3.28, J8.28, J14.28, J16.28, J19.28, J24.5
/MD5: J3.27, J8.27, J14.27, J16.27, J19.27, J24.6
/MD6: J3.30, J8.30, J14.30, J16.30, J19.30, J24.3
/MD7: J3.29, J8.29, J14.29, J16.29, J19.29, J24.4
/PDLTRIG: J2.7, J7.7, J9.7, J13.7, J18.7, J23.7
/PH0: J4.8, J10.8, J11.8, J15.8, J20.8, J25.8
/Q3: J4.6, J10.6, J11.6, J15.6, J20.6, J25.6
/RW: J4.5, J10.5, J11.5, J15.5, J20.5, J25.5
/~DMA: J2.5, J7.5, J9.5, J13.5, J18.5, J23.5
/~INH: J4.7, J10.7, J11.7, J15.7, J20.7, J25.7
/~IRQ: J4.1, J10.1, J11.1, J15.1, J20.1, J25.1
/~NMI: J2.3, J7.3, J9.3, J13.3, J18.3, J23.3
/~RDY: J2.1, J7.1, J9.1, J13.1, J18.1, J23.1
/~RESET: J4.3, J10.3, J11.3, J15.3, J20.3, J25.3
GND: C5.2, C6.2, C7.2, D1.1, D2.1, J1.1, J1.2, J2.9, J2.10, J3.1, J3.2, J3.11, J3.12, J3.21, J3.22, J3.31, J3.32, J4.9, J4.10, J5.1, J5.2, J6.1, J6.2, J7.9, J7.10, J8.1, J8.2, J8.11, J8.12, J8.21, J8.22, J8.31, J8.32, J9.9, J9.10, J10.9, J10.10, J11.9, J11.10, J12.1, J12.2, J13.9, J13.10, J14.1, J14.2, J14.11, J14.12, J14.21, J14.22, J14.31, J14.32, J15.9, J15.10, J16.1, J16.2, J16.11, J16.12, J16.21, J16.22, J16.31, J16.32, J17.1, J17.2, J18.9, J18.10, J19.1, J19.2, J19.11, J19.12, J19.21, J19.22, J19.31, J19.32, J20.9, J20.10, J22.1, J22.2, J23.9, J23.10, J24.1, J24.2, J24.11, J24.12, J24.21, J24.22, J24.31, J24.32, J25.9, J25.10, R3.2
unnamed: D1.2, R1.2
unnamed: D2.2, R2.2
unnamed: D3.2, R3.1

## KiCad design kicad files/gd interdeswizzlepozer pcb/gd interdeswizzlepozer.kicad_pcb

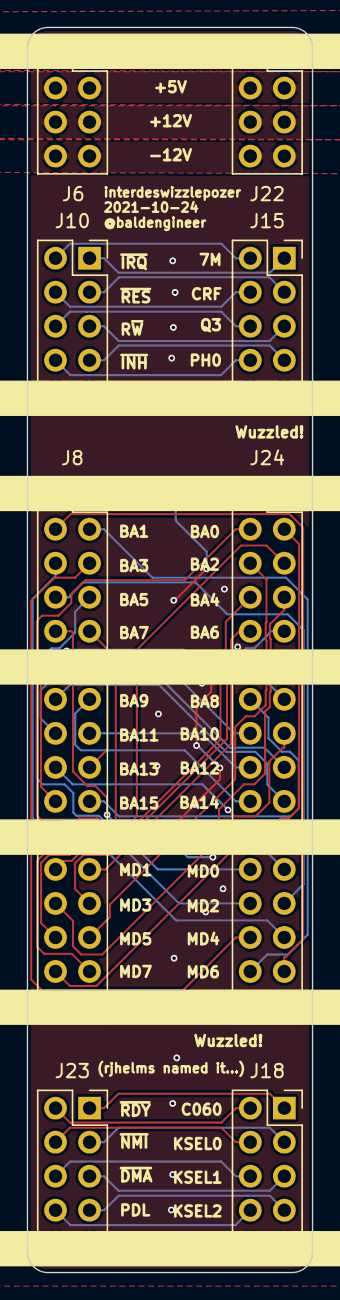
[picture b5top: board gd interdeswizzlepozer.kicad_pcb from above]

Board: 2 copper layers, 21.3 x 93.0 mm, 8 parts (0 on the bottom side), 44 nets.

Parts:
J6, J22: Pwr; PinSocket_2x04_P2.54mm_Vertical
J8, J24: Addr_Main_Data; PinSocket_2x16_P2.54mm_Vertical
J10, J15: CTRL1; PinSocket_2x05_P2.54mm_Vertical
J18, J23: CTRL2; PinSocket_2x05_P2.54mm_Vertical

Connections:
+5V: J6.3, J6.4, J22.3, J22.4
+12V: J6.5, J6.6, J22.5, J22.6
-12V: J6.7, J6.8, J22.7, J22.8
/7M: J10.2, J15.2
/BA0: J8.4, J24.29
/BA1: J8.3, J24.30
/BA2: J8.6, J24.27
/BA3: J8.5, J24.28
/BA4: J8.8, J24.25
/BA5: J8.7, J24.26
/BA6: J8.10, J24.23
/BA7: J8.9, J24.24
/BA8: J8.14, J24.19
/BA9: J8.13, J24.20
/BA10: J8.16, J24.17
/BA11: J8.15, J24.18
/BA12: J8.18, J24.15
/BA13: J8.17, J24.16
/BA14: J8.20, J24.13
/BA15: J8.19, J24.14
/C060-67: J18.2, J23.2
/CREF: J10.4, J15.4
/GND: J6.1, J6.2, J8.1, J8.2, J8.11, J8.12, J8.21, J8.22, J8.31, J8.32, J10.9, J10.10, J15.9, J15.10, J18.9, J18.10, J22.1, J22.2, J23.9, J23.10, J24.1, J24.2, J24.11, J24.12, J24.21, J24.22, J24.31, J24.32
/KSEL0: J18.4, J23.4
/KSEL1: J18.6, J23.6
/KSEL2: J18.8, J23.8
/MD0: J8.24, J24.9
/MD1: J8.23, J24.10
/MD2: J8.26, J24.7
/MD3: J8.25, J24.8
/MD4: J8.28, J24.5
/MD5: J8.27, J24.6
/MD6: J8.30, J24.3
/MD7: J8.29, J24.4
/PDLTRIG: J18.7, J23.7
/PH0: J10.8, J15.8
/Q3: J10.6, J15.6
/RW: J10.5, J15.5
/~DMA: J18.5, J23.5
/~INH: J10.7, J15.7
/~IRQ: J10.1, J15.1
/~NMI: J18.3, J23.3
/~RDY: J18.1, J23.1
/~RESET: J10.3, J15.3

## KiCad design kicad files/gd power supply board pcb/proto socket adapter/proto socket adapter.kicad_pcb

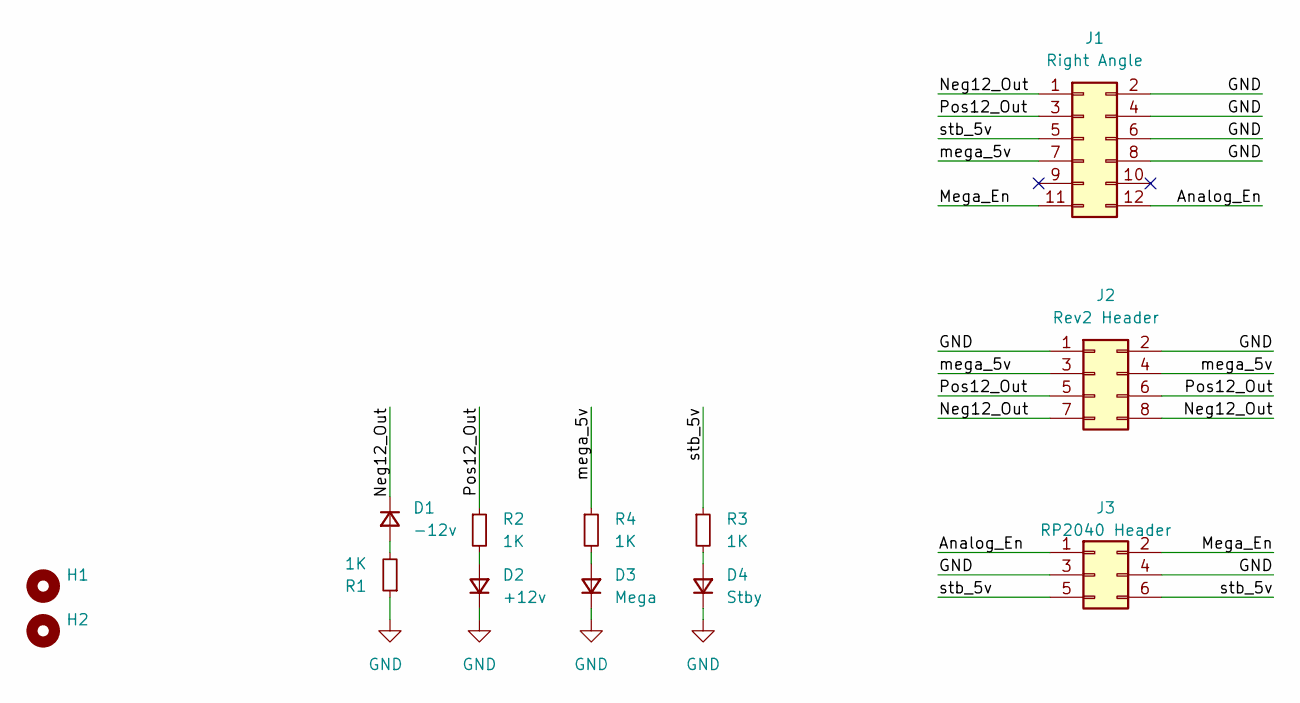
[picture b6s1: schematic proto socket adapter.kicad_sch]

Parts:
D1: -12v; LED_0805_2012Metric
D2: +12v; LED_0805_2012Metric
D3: Mega; LED_0805_2012Metric
D4: Stby; LED_0805_2012Metric
H1, H2: MountingHole; MountingHole_2.2mm_M2
J1: Right Angle; TE 5650118-3 Right Angle 12 Pos Socket
J2: Rev2 Header; PinSocket_2x04_P2.54mm_Vertical
J3: RP2040 Header; PinSocket_2x03_P2.54mm_Vertical
R1, R2, R3, R4: 1K; R_0805_2012Metric

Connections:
/Analog_En: J1.12, J3.1
/Mega_En: J1.11, J3.2
/Neg12_Out: D1.1 (K), J1.1, J2.7, J2.8
/Pos12_Out: J1.3, J2.5, J2.6, R2.1
/mega_5v: J1.7, J2.3, J2.4, R4.1
/stb_5v: J1.5, J3.5, J3.6, R3.1
GND: D2.1 (K), D3.1 (K), D4.1 (K), J1.2, J1.4, J1.6, J1.8, J2.1, J2.2, J3.3, J3.4, R1.1
unnamed: D1.2 (A), R1.2
unnamed: D2.2 (A), R2.2
unnamed: D3.2 (A), R4.2
unnamed: D4.2 (A), R3.2
